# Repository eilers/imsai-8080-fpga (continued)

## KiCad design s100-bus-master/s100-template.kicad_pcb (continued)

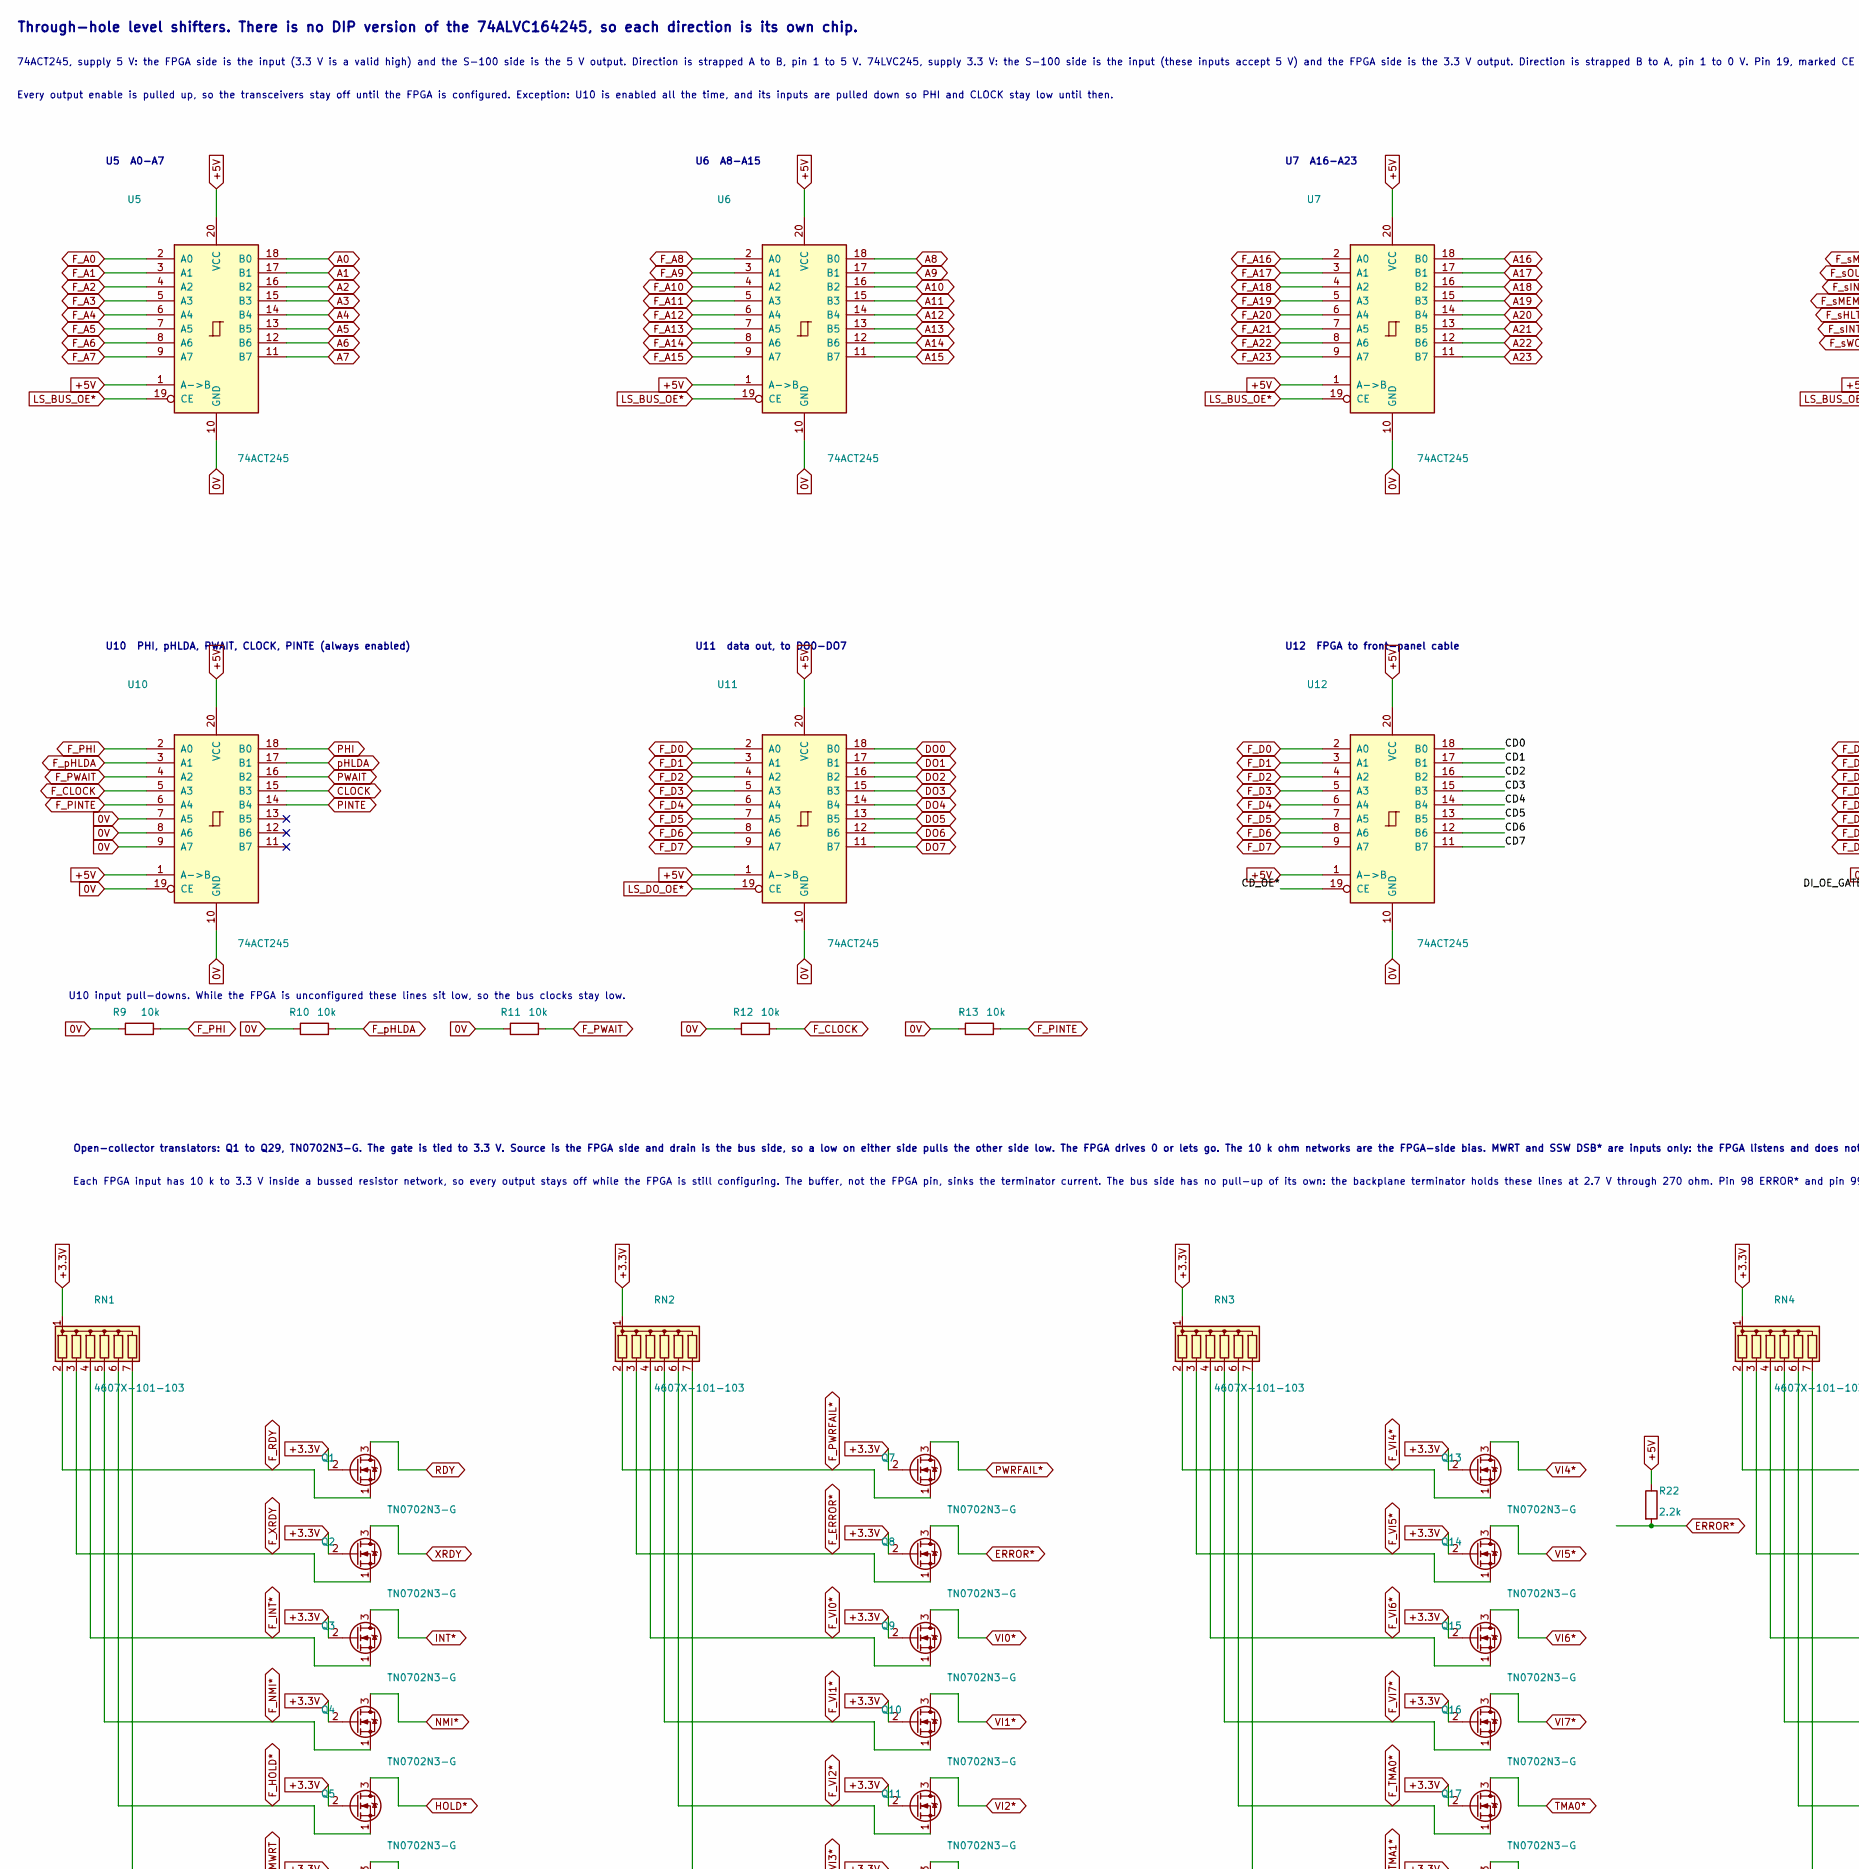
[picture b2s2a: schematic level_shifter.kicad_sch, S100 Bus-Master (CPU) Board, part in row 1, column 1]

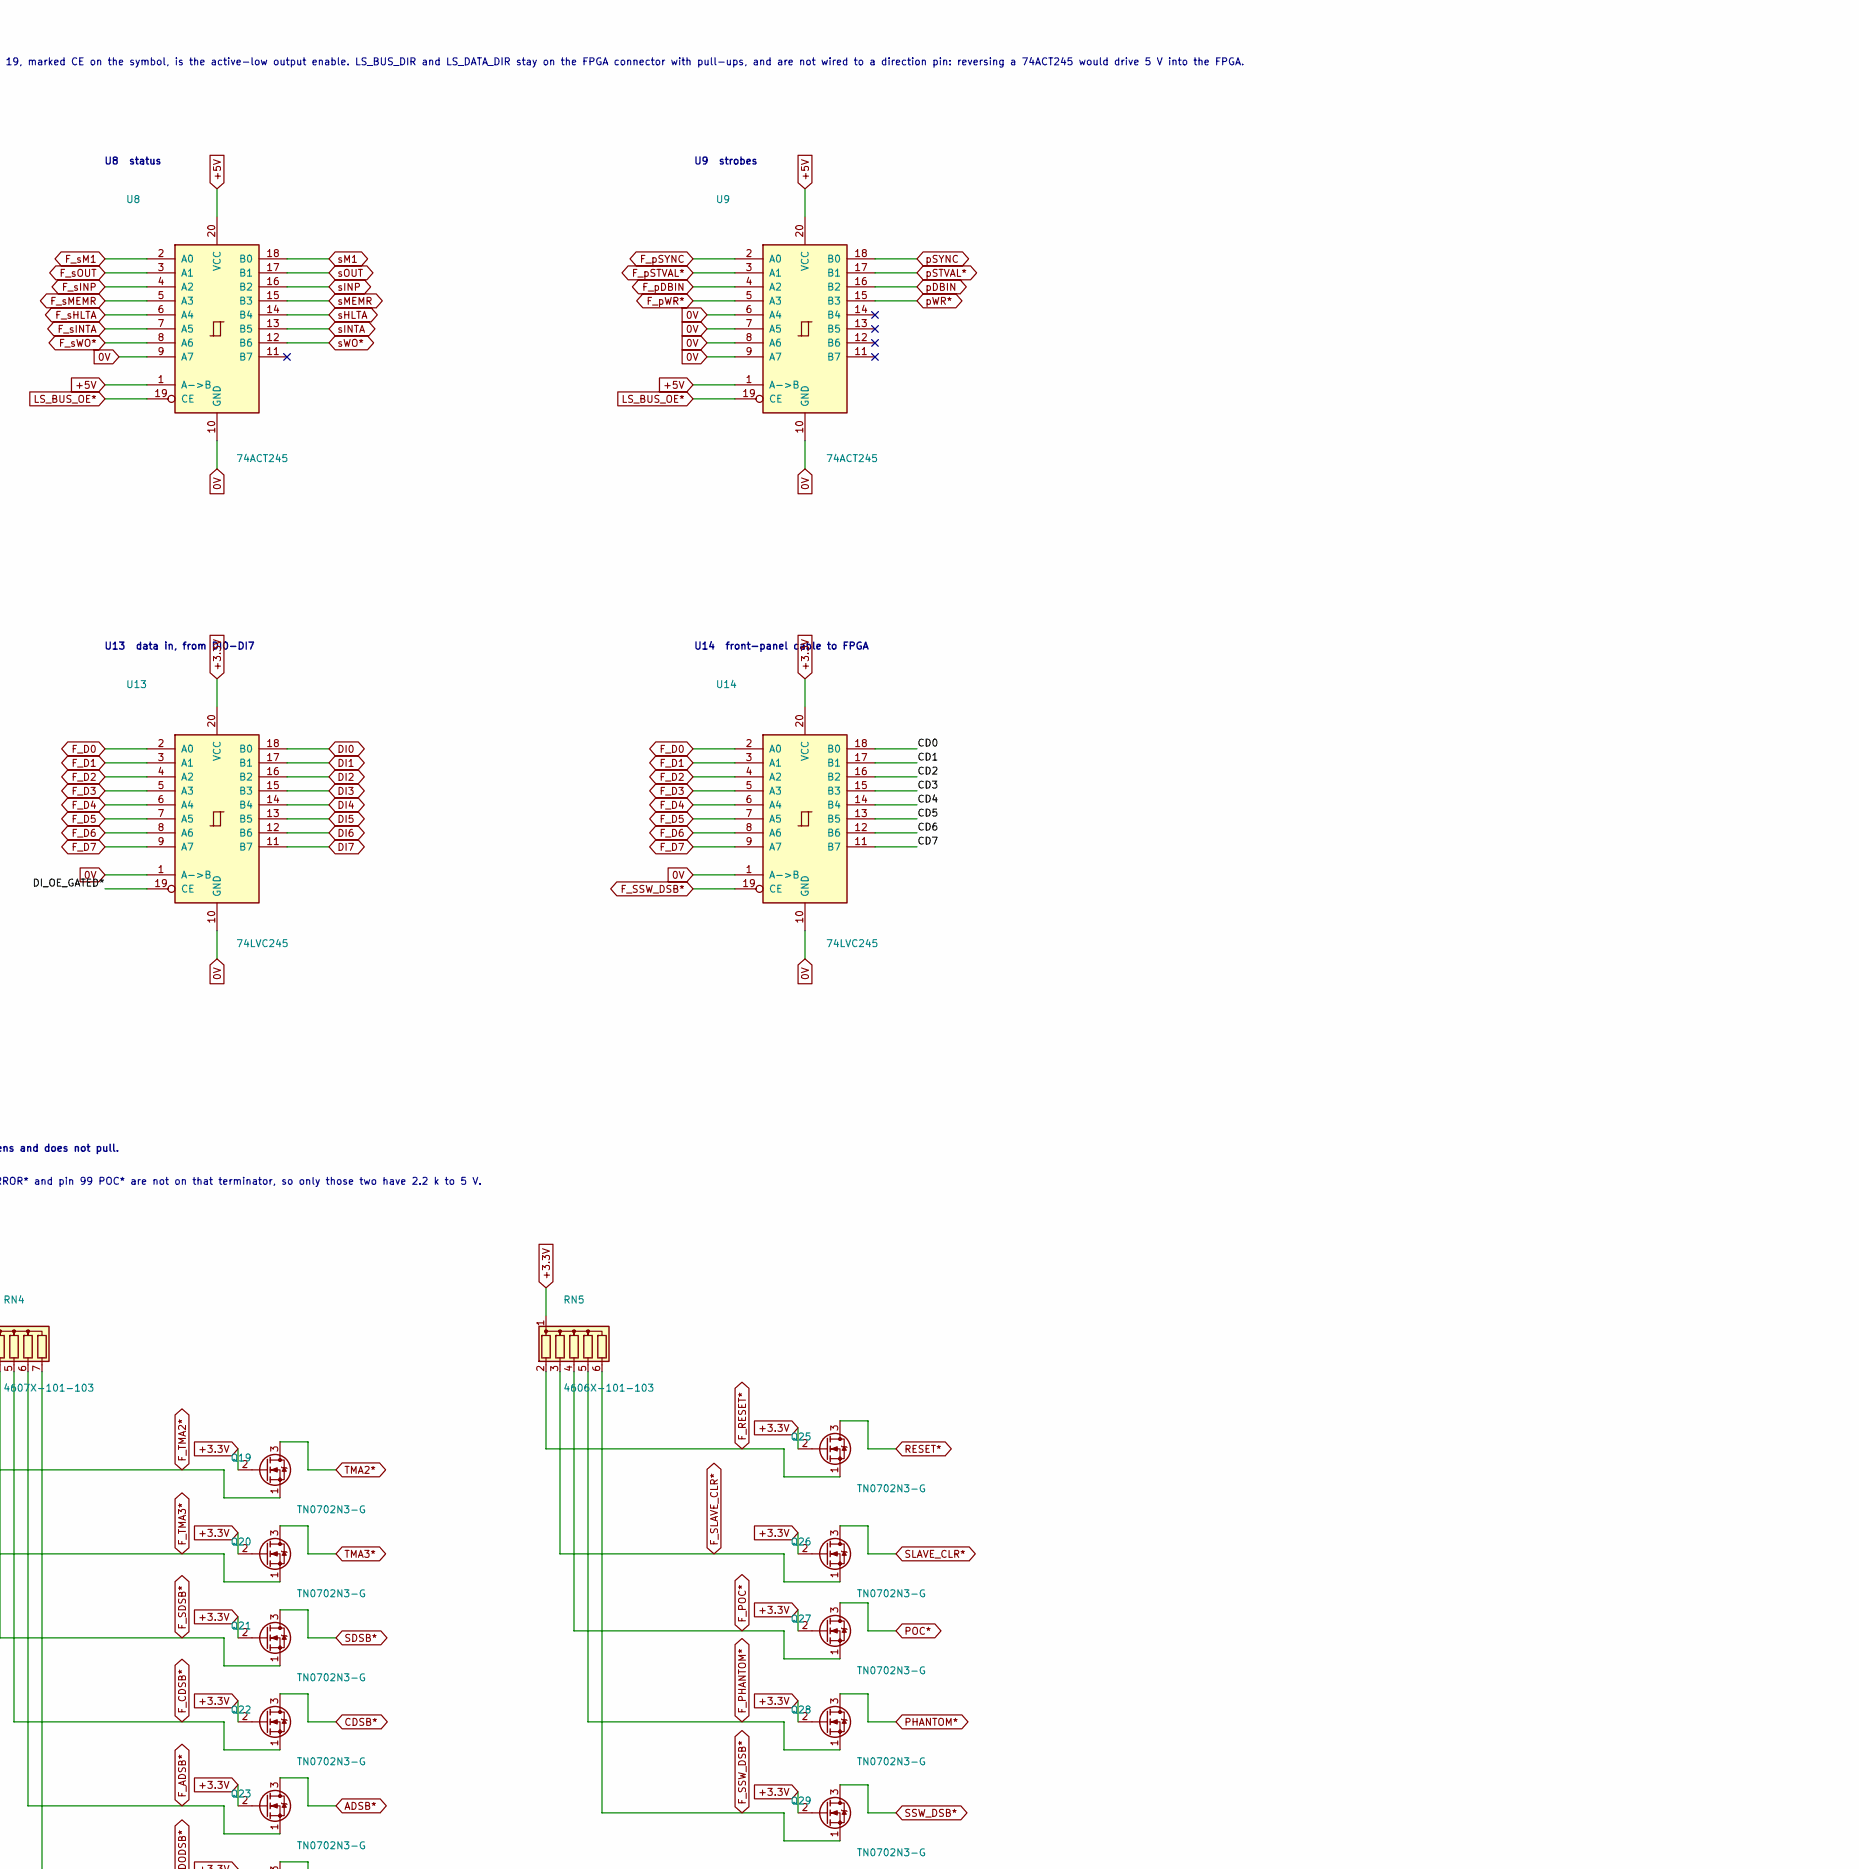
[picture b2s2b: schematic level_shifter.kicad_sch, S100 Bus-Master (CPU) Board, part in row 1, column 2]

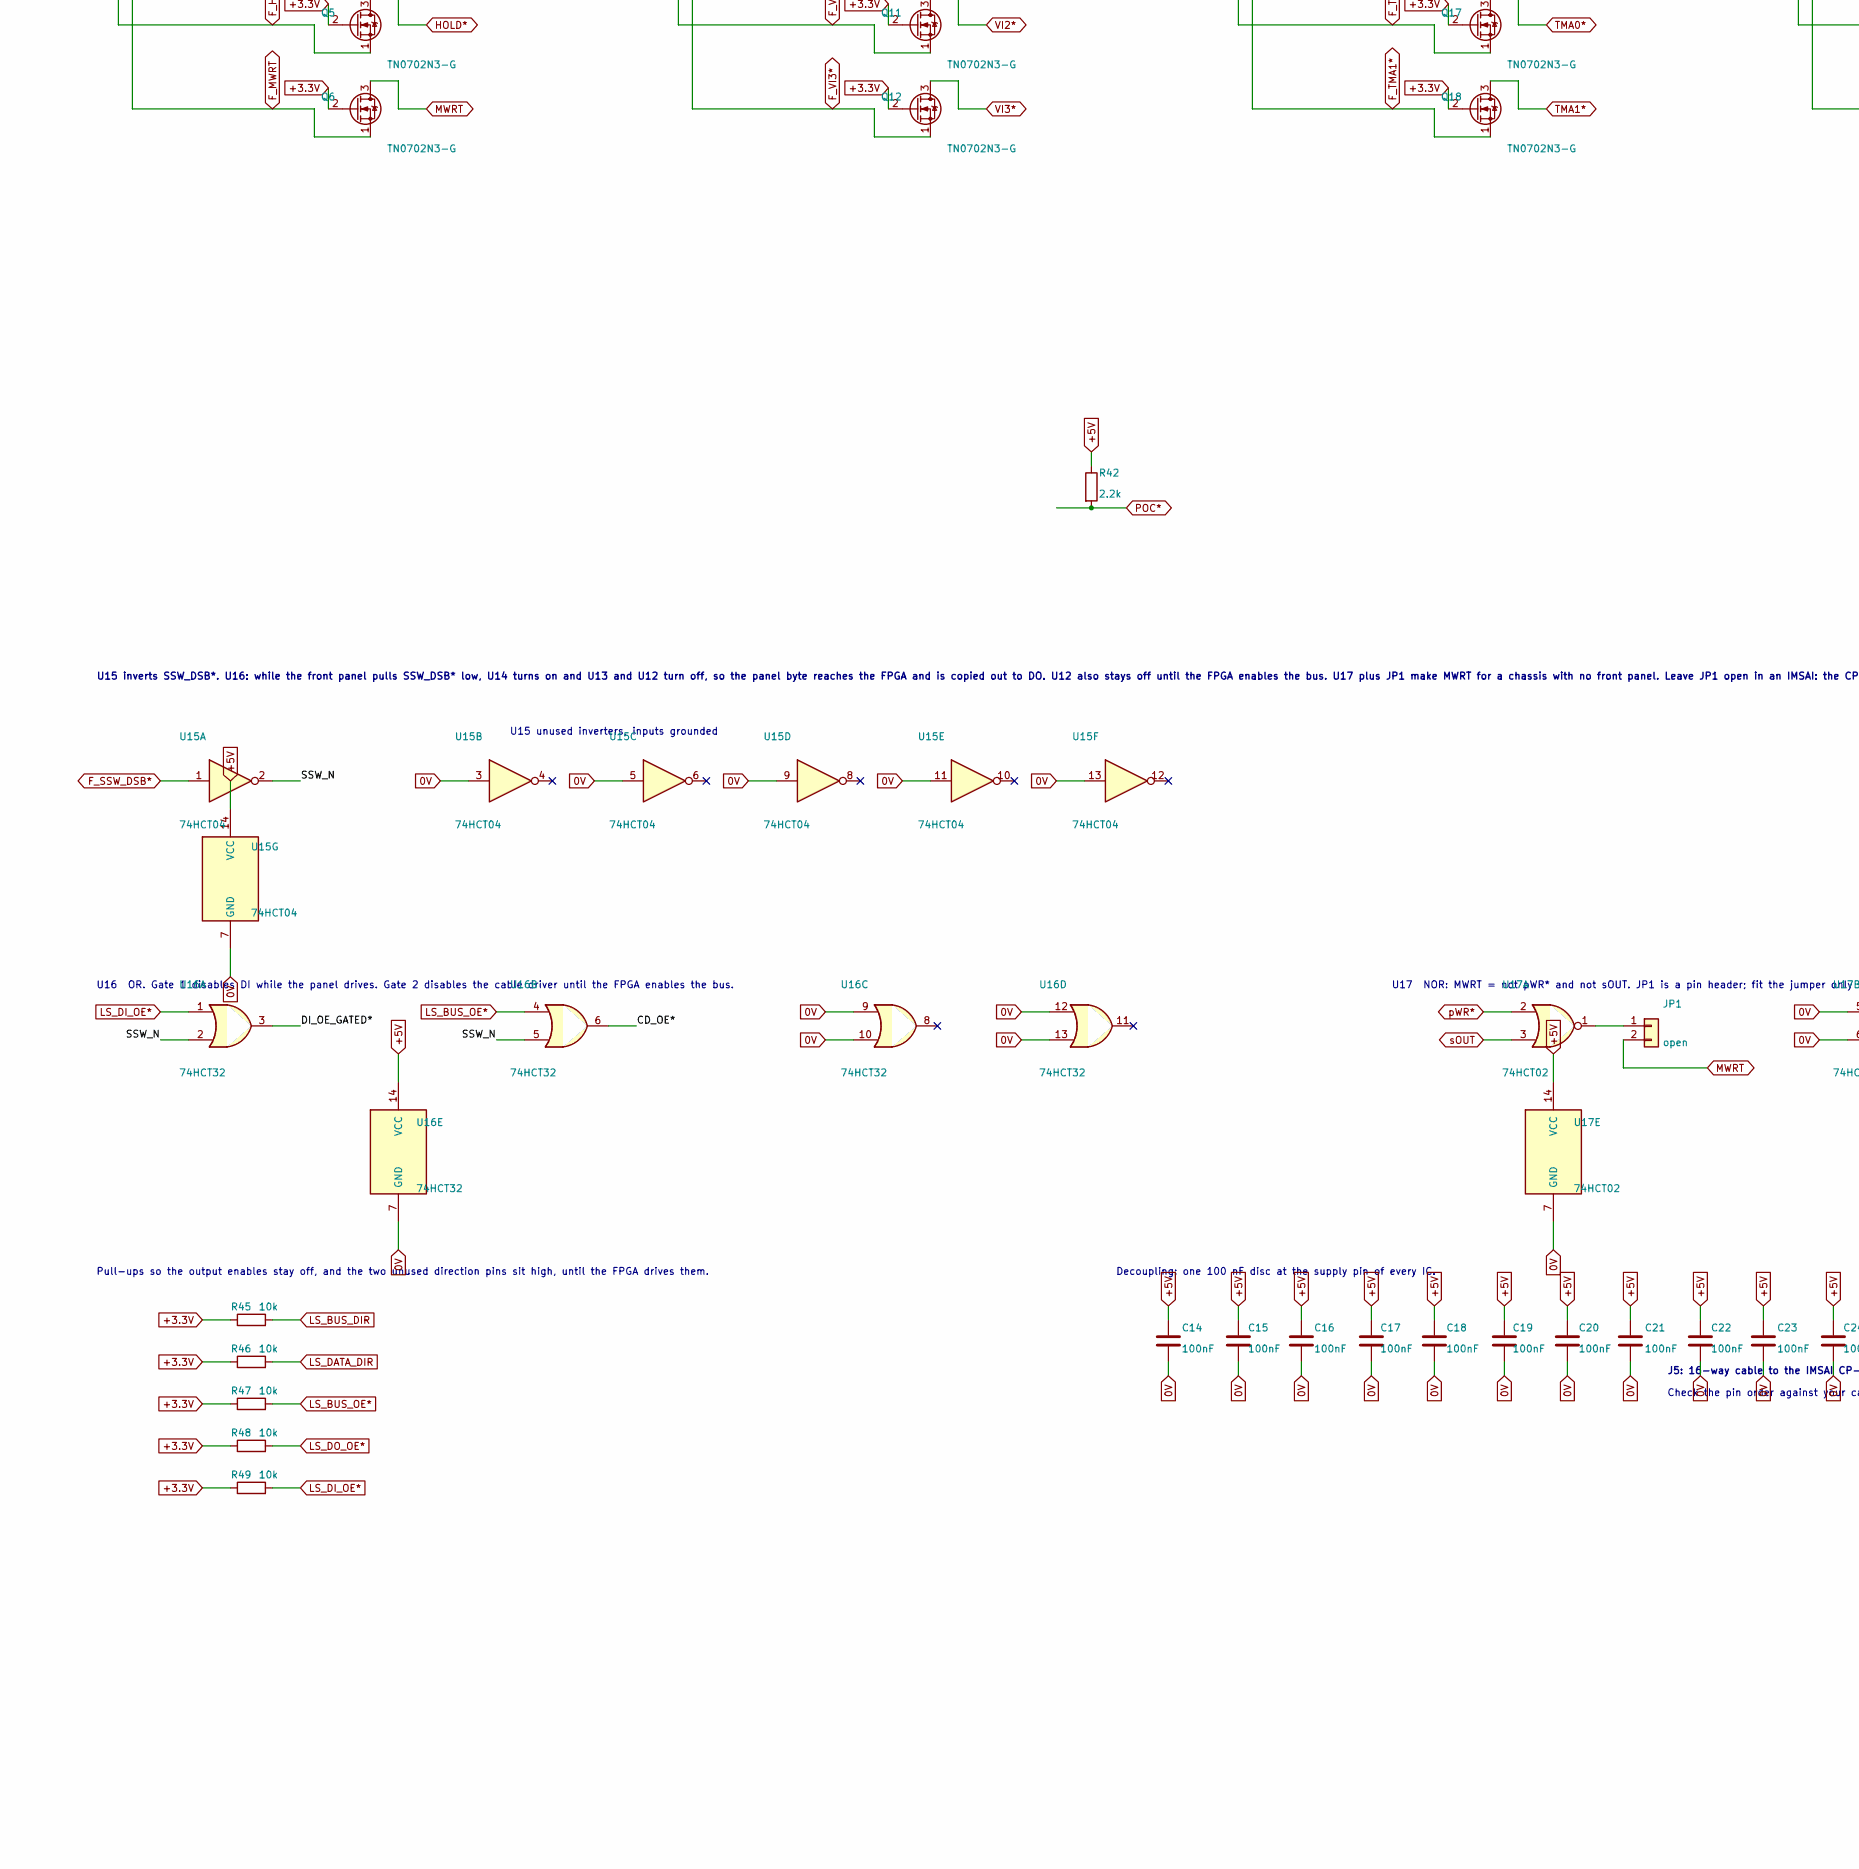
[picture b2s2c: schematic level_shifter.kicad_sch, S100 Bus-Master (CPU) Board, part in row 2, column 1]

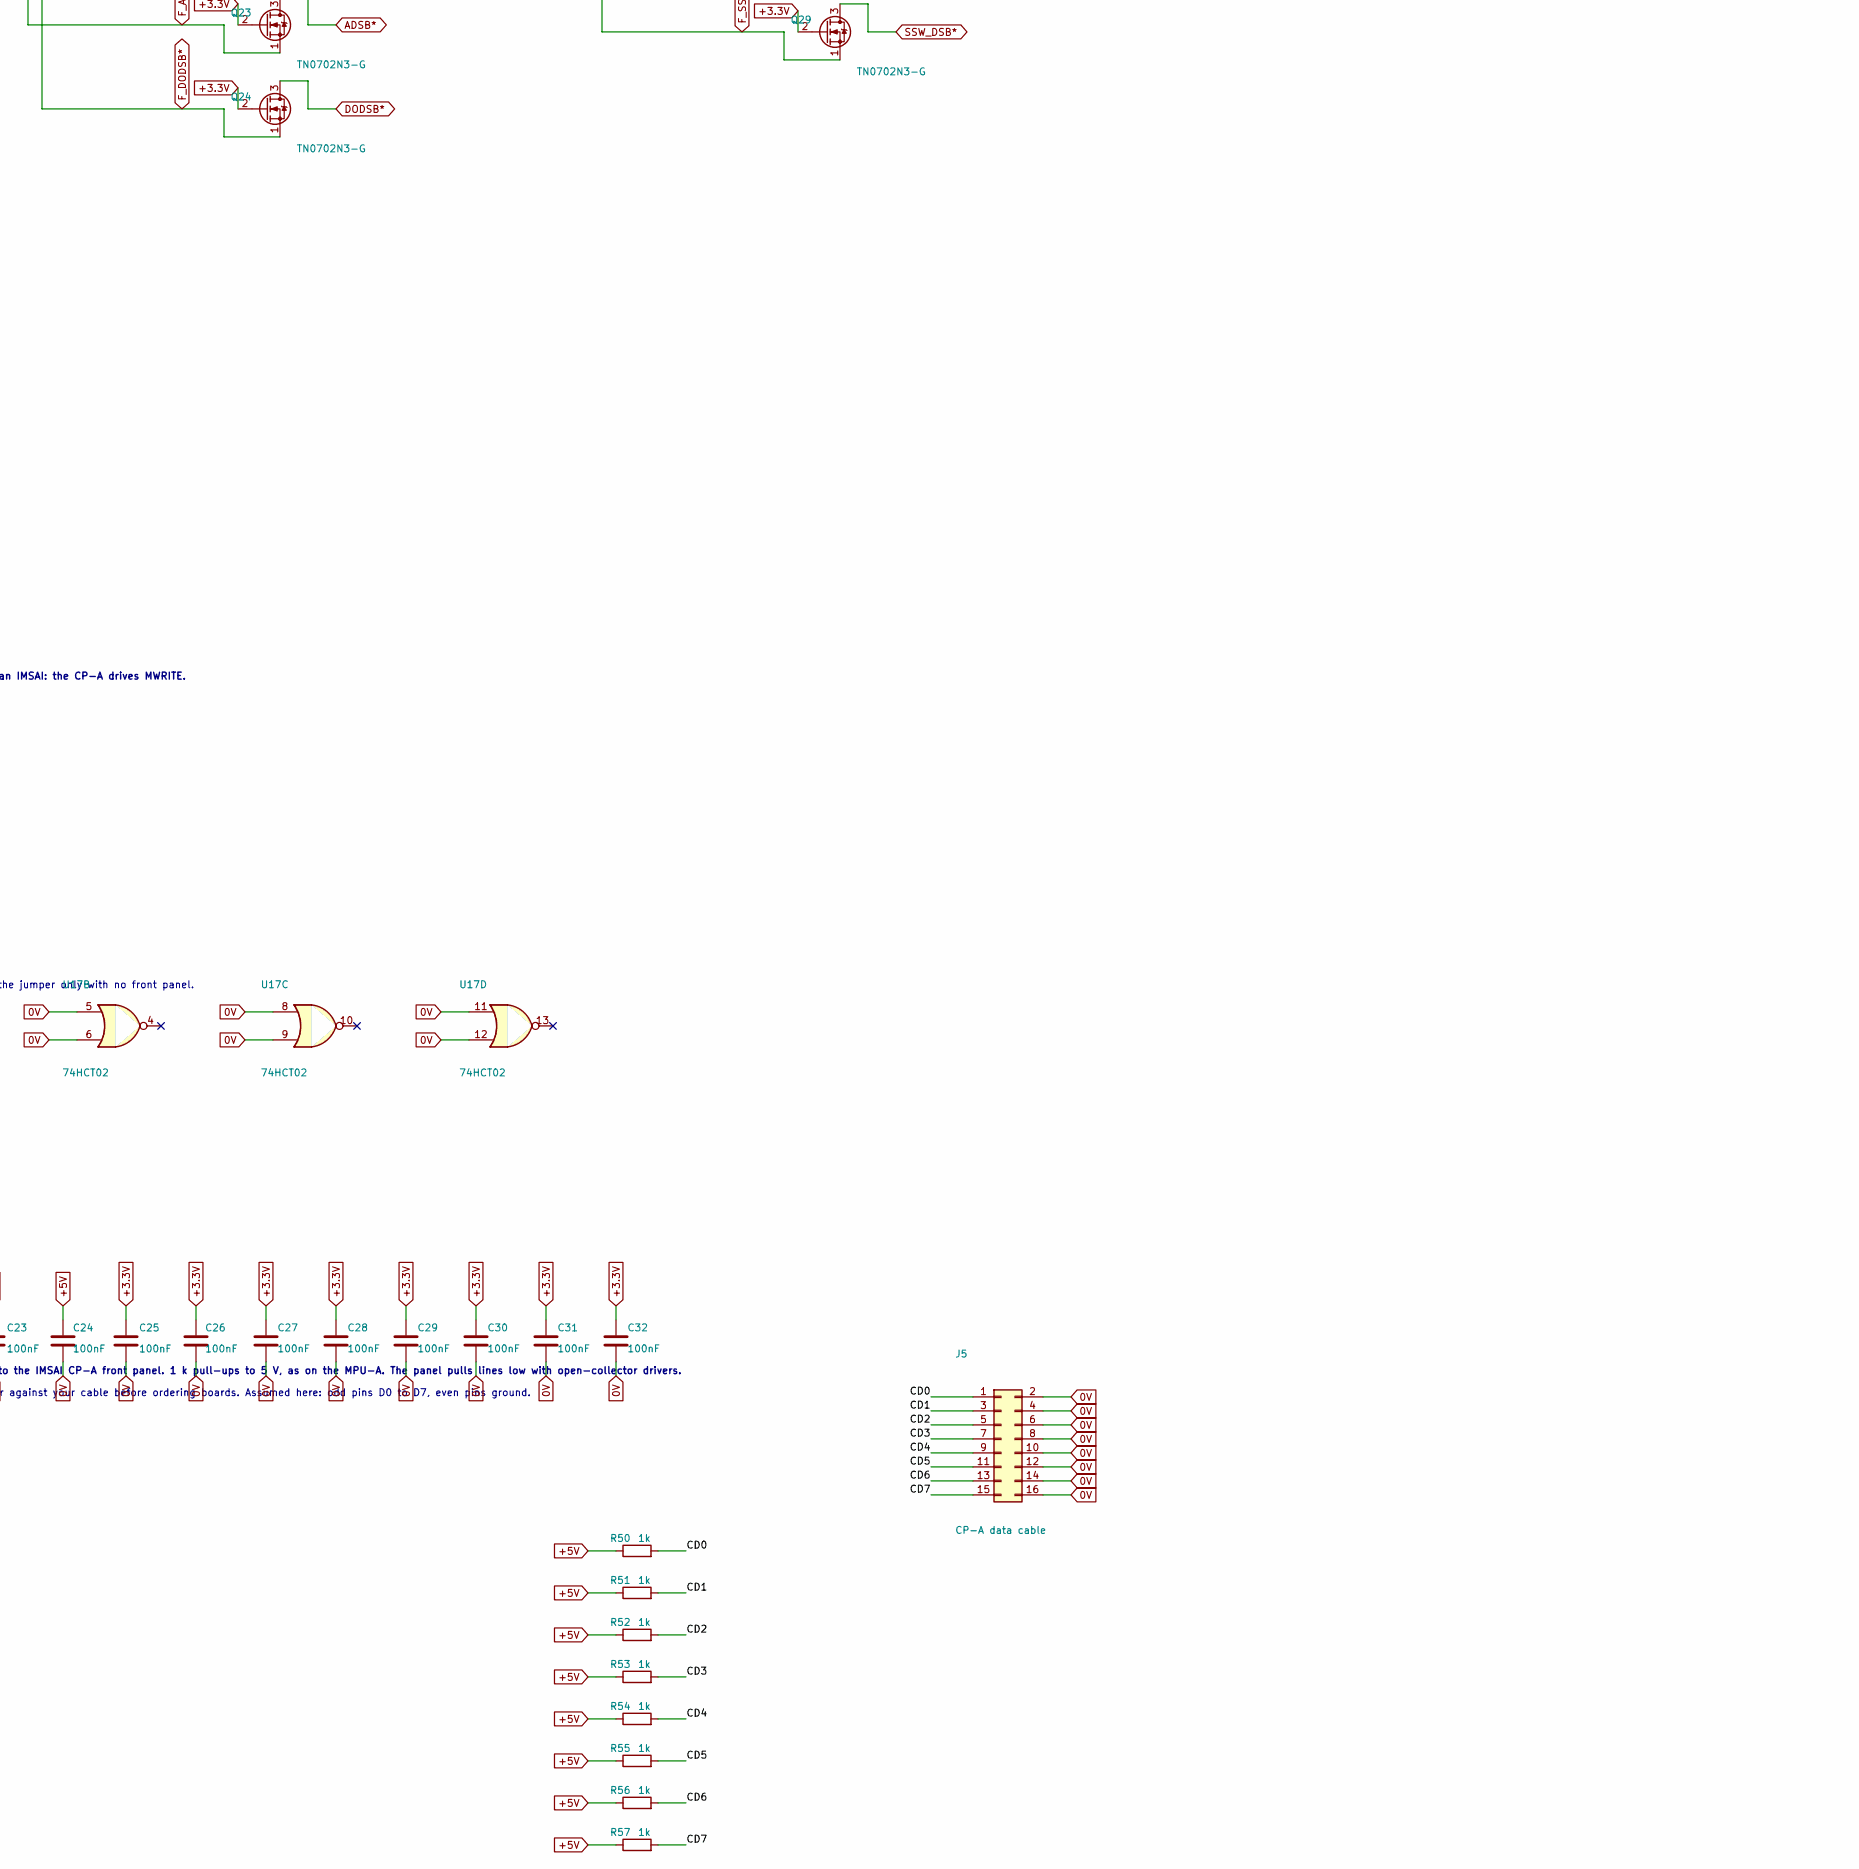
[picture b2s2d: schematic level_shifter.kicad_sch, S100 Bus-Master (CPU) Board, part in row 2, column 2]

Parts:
C14, C15, C16, C17, C18, C19, C20, C21, C22, C23, C24, C25, C26, C27, C28, C29, C30, C31, C32: 100nF; C_Disc_D5.0mm_W2.5mm_P5.00mm
J5: CP-A data cable; IDC-Header_2x08_P2.54mm_Vertical
JP1: open; PinHeader_1x02_P2.54mm_Vertical
Q1, Q2, Q3, Q4, Q5, Q6, Q7, Q8, Q9, Q10, Q11, Q12, Q13, Q14, Q15, Q16, Q17, Q18, Q19, Q20, Q21, Q22, Q23, Q24, Q25, Q26, Q27, Q28, Q29: TN0702N3-G; TO-92
R9, R10, R11, R12, R13, R45, R46, R47, R48, R49: 10k; R_Axial_DIN0207_L6.3mm_D2.5mm_P10.16mm_Horizontal
R22, R42: 2.2k; R_Axial_DIN0207_L6.3mm_D2.5mm_P10.16mm_Horizontal
R50, R51, R52, R53, R54, R55, R56, R57: 1k; R_Axial_DIN0207_L6.3mm_D2.5mm_P10.16mm_Horizontal
RN1, RN2, RN3, RN4: 4607X-101-103; R_Array_SIP7
RN5: 4606X-101-103; R_Array_SIP6
U5, U6, U7, U8, U9, U10, U11, U12: 74ACT245; DIP-20_W7.62mm
U13, U14: 74LVC245; DIP-20_W7.62mm
U15: 74HCT04; DIP-14_W7.62mm
U16: 74HCT32; DIP-14_W7.62mm
U17: 74HCT02; DIP-14_W7.62mm

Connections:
0V: C14.2, C15.2, C16.2, C17.2, C18.2, C19.2, C20.2, C21.2, C22.2, C23.2, C24.2, C25.2, C26.2, C27.2, C28.2, C29.2, C30.2, C31.2, C32.2, J5.2, J5.4, J5.6, J5.8, J5.10, J5.12, J5.14, J5.16, R9.1, R10.1, R11.1, R12.1, R13.1, U5.10 (GND), U6.10 (GND), U7.10 (GND), U8.9 (A7), U8.10 (GND), U9.6 (A4), U9.7 (A5), U9.8 (A6), U9.9 (A7), U9.10 (GND), U10.7 (A5), U10.8 (A6), U10.9 (A7), U10.10 (GND), U10.19 (CE), U11.10 (GND), U12.10 (GND), U13.1 (A->B), U13.10 (GND), U14.1 (A->B), U14.10 (GND), U15.3, U15.5, U15.7 (GND), U15.9, U15.11, U15.13, U16.7 (GND), U16.9, U16.10, U16.12, U16.13, U17.5, U17.6, U17.7 (GND), U17.8, U17.9, U17.11, U17.12; also elsewhere on the board
+3.3V: C25.1, C26.1, C27.1, C28.1, C29.1, C30.1, C31.1, C32.1, Q1.2 (G), Q2.2 (G), Q3.2 (G), Q4.2 (G), Q5.2 (G), Q6.2 (G), Q7.2 (G), Q8.2 (G), Q9.2 (G), Q10.2 (G), Q11.2 (G), Q12.2 (G), Q13.2 (G), Q14.2 (G), Q15.2 (G), Q16.2 (G), Q17.2 (G), Q18.2 (G), Q19.2 (G), Q20.2 (G), Q21.2 (G), Q22.2 (G), Q23.2 (G), Q24.2 (G), Q25.2 (G), Q26.2 (G), Q27.2 (G), Q28.2 (G), Q29.2 (G), R45.1, R46.1, R47.1, R48.1, R49.1, RN1.1 (common), RN2.1 (common), RN3.1 (common), RN4.1 (common), RN5.1 (common), U13.20 (VCC), U14.20 (VCC); also elsewhere on the board
+5V: C14.1, C15.1, C16.1, C17.1, C18.1, C19.1, C20.1, C21.1, C22.1, C23.1, C24.1, R22.1, R42.1, R50.1, R51.1, R52.1, R53.1, R54.1, R55.1, R56.1, R57.1, U5.1 (A->B), U5.20 (VCC), U6.1 (A->B), U6.20 (VCC), U7.1 (A->B), U7.20 (VCC), U8.1 (A->B), U8.20 (VCC), U9.1 (A->B), U9.20 (VCC), U10.1 (A->B), U10.20 (VCC), U11.1 (A->B), U11.20 (VCC), U12.1 (A->B), U12.20 (VCC), U15.14 (VCC), U16.14 (VCC), U17.14 (VCC); also elsewhere on the board
/Level Shifter/CD0: J5.1, R50.2, U12.18 (B0), U14.18 (B0)
/Level Shifter/CD1: J5.3, R51.2, U12.17 (B1), U14.17 (B1)
/Level Shifter/CD2: J5.5, R52.2, U12.16 (B2), U14.16 (B2)
/Level Shifter/CD3: J5.7, R53.2, U12.15 (B3), U14.15 (B3)
/Level Shifter/CD4: J5.9, R54.2, U12.14 (B4), U14.14 (B4)
/Level Shifter/CD5: J5.11, R55.2, U12.13 (B5), U14.13 (B5)
/Level Shifter/CD6: J5.13, R56.2, U12.12 (B6), U14.12 (B6)
/Level Shifter/CD7: J5.15, R57.2, U12.11 (B7), U14.11 (B7)
/Level Shifter/CD_OE*: U12.19 (CE), U16.6
/Level Shifter/DI_OE_GATED*: U13.19 (CE), U16.3
/Level Shifter/SSW_N: U15.2, U16.2, U16.5
A0: U5.18 (B0); also elsewhere on the board
A1: U5.17 (B1); also elsewhere on the board
A2: U5.16 (B2); also elsewhere on the board
A3: U5.15 (B3); also elsewhere on the board
A4: U5.14 (B4); also elsewhere on the board
A5: U5.13 (B5); also elsewhere on the board
A6: U5.12 (B6); also elsewhere on the board
A7: U5.11 (B7); also elsewhere on the board
A8: U6.18 (B0); also elsewhere on the board
A9: U6.17 (B1); also elsewhere on the board
A10: U6.16 (B2); also elsewhere on the board
A11: U6.15 (B3); also elsewhere on the board
A12: U6.14 (B4); also elsewhere on the board
A13: U6.13 (B5); also elsewhere on the board
A14: U6.12 (B6); also elsewhere on the board
A15: U6.11 (B7); also elsewhere on the board
A16: U7.18 (B0); also elsewhere on the board
A17: U7.17 (B1); also elsewhere on the board
A18: U7.16 (B2); also elsewhere on the board
A19: U7.15 (B3); also elsewhere on the board
A20: U7.14 (B4); also elsewhere on the board
A21: U7.13 (B5); also elsewhere on the board
A22: U7.12 (B6); also elsewhere on the board
A23: U7.11 (B7); also elsewhere on the board
ADSB*: Q23.3 (D); also elsewhere on the board
CDSB*: Q22.3 (D); also elsewhere on the board
CLOCK: U10.15 (B3); also elsewhere on the board
DI0: U13.18 (B0); also elsewhere on the board
DI1: U13.17 (B1); also elsewhere on the board
DI2: U13.16 (B2); also elsewhere on the board
DI3: U13.15 (B3); also elsewhere on the board
DI4: U13.14 (B4); also elsewhere on the board
DI5: U13.13 (B5); also elsewhere on the board
DI6: U13.12 (B6); also elsewhere on the board
DI7: U13.11 (B7); also elsewhere on the board
DO0: U11.18 (B0); also elsewhere on the board
DO1: U11.17 (B1); also elsewhere on the board
DO2: U11.16 (B2); also elsewhere on the board
DO3: U11.15 (B3); also elsewhere on the board
DO4: U11.14 (B4); also elsewhere on the board
DO5: U11.13 (B5); also elsewhere on the board
DO6: U11.12 (B6); also elsewhere on the board
DO7: U11.11 (B7); also elsewhere on the board
DODSB*: Q24.3 (D); also elsewhere on the board
ERROR*: Q8.3 (D), R22.2; also elsewhere on the board
F_A0: U5.2 (A0); also elsewhere on the board
F_A1: U5.3 (A1); also elsewhere on the board
F_A2: U5.4 (A2); also elsewhere on the board
F_A3: U5.5 (A3); also elsewhere on the board
F_A4: U5.6 (A4); also elsewhere on the board
F_A5: U5.7 (A5); also elsewhere on the board
F_A6: U5.8 (A6); also elsewhere on the board
F_A7: U5.9 (A7); also elsewhere on the board
F_A8: U6.2 (A0); also elsewhere on the board
F_A9: U6.3 (A1); also elsewhere on the board
F_A10: U6.4 (A2); also elsewhere on the board
F_A11: U6.5 (A3); also elsewhere on the board
F_A12: U6.6 (A4); also elsewhere on the board
F_A13: U6.7 (A5); also elsewhere on the board
F_A14: U6.8 (A6); also elsewhere on the board
F_A15: U6.9 (A7); also elsewhere on the board
F_A16: U7.2 (A0); also elsewhere on the board
F_A17: U7.3 (A1); also elsewhere on the board
F_A18: U7.4 (A2); also elsewhere on the board
F_A19: U7.5 (A3); also elsewhere on the board
F_A20: U7.6 (A4); also elsewhere on the board
F_A21: U7.7 (A5); also elsewhere on the board
F_A22: U7.8 (A6); also elsewhere on the board
F_A23: U7.9 (A7); also elsewhere on the board
F_ADSB*: Q23.1 (S), RN4.6 (R5); also elsewhere on the board
F_CDSB*: Q22.1 (S), RN4.5 (R4); also elsewhere on the board
F_CLOCK: R12.2, U10.5 (A3); also elsewhere on the board
F_D0: U11.2 (A0), U12.2 (A0), U13.2 (A0), U14.2 (A0); also elsewhere on the board
F_D1: U11.3 (A1), U12.3 (A1), U13.3 (A1), U14.3 (A1); also elsewhere on the board
F_D2: U11.4 (A2), U12.4 (A2), U13.4 (A2), U14.4 (A2); also elsewhere on the board
F_D3: U11.5 (A3), U12.5 (A3), U13.5 (A3), U14.5 (A3); also elsewhere on the board
F_D4: U11.6 (A4), U12.6 (A4), U13.6 (A4), U14.6 (A4); also elsewhere on the board
F_D5: U11.7 (A5), U12.7 (A5), U13.7 (A5), U14.7 (A5); also elsewhere on the board
F_D6: U11.8 (A6), U12.8 (A6), U13.8 (A6), U14.8 (A6); also elsewhere on the board
F_D7: U11.9 (A7), U12.9 (A7), U13.9 (A7), U14.9 (A7); also elsewhere on the board
F_DODSB*: Q24.1 (S), RN4.7 (R6); also elsewhere on the board
F_ERROR*: Q8.1 (S), RN2.3 (R2); also elsewhere on the board
F_HOLD*: Q5.1 (S), RN1.6 (R5); also elsewhere on the board
F_INT*: Q3.1 (S), RN1.4 (R3); also elsewhere on the board
F_MWRT: Q6.1 (S), RN1.7 (R6); also elsewhere on the board
F_NMI*: Q4.1 (S), RN1.5 (R4); also elsewhere on the board
F_PHANTOM*: Q28.1 (S), RN5.5 (R4); also elsewhere on the board
F_PHI: R9.2, U10.2 (A0); also elsewhere on the board
F_PINTE: R13.2, U10.6 (A4); also elsewhere on the board
F_POC*: Q27.1 (S), RN5.4 (R3); also elsewhere on the board
F_PWAIT: R11.2, U10.4 (A2); also elsewhere on the board
F_PWRFAIL*: Q7.1 (S), RN2.2 (R1); also elsewhere on the board
F_RDY: Q1.1 (S), RN1.2 (R1); also elsewhere on the board
F_RESET*: Q25.1 (S), RN5.2 (R1); also elsewhere on the board
F_SDSB*: Q21.1 (S), RN4.4 (R3); also elsewhere on the board
F_SLAVE_CLR*: Q26.1 (S), RN5.3 (R2); also elsewhere on the board
F_SSW_DSB*: Q29.1 (S), RN5.6 (R5), U14.19 (CE), U15.1; also elsewhere on the board
F_TMA0*: Q17.1 (S), RN3.6 (R5); also elsewhere on the board
F_TMA1*: Q18.1 (S), RN3.7 (R6); also elsewhere on the board
F_TMA2*: Q19.1 (S), RN4.2 (R1); also elsewhere on the board
F_TMA3*: Q20.1 (S), RN4.3 (R2); also elsewhere on the board
F_VI0*: Q9.1 (S), RN2.4 (R3); also elsewhere on the board
F_VI1*: Q10.1 (S), RN2.5 (R4); also elsewhere on the board
F_VI2*: Q11.1 (S), RN2.6 (R5); also elsewhere on the board
F_VI3*: Q12.1 (S), RN2.7 (R6); also elsewhere on the board
F_VI4*: Q13.1 (S), RN3.2 (R1); also elsewhere on the board
F_VI5*: Q14.1 (S), RN3.3 (R2); also elsewhere on the board
F_VI6*: Q15.1 (S), RN3.4 (R3); also elsewhere on the board
F_VI7*: Q16.1 (S), RN3.5 (R4); also elsewhere on the board
F_XRDY: Q2.1 (S), RN1.3 (R2); also elsewhere on the board
F_pDBIN: U9.4 (A2); also elsewhere on the board
F_pHLDA: R10.2, U10.3 (A1); also elsewhere on the board
F_pSTVAL*: U9.3 (A1); also elsewhere on the board
F_pSYNC: U9.2 (A0); also elsewhere on the board
F_pWR*: U9.5 (A3); also elsewhere on the board
F_sHLTA: U8.6 (A4); also elsewhere on the board
F_sINP: U8.4 (A2); also elsewhere on the board
F_sINTA: U8.7 (A5); also elsewhere on the board
F_sM1: U8.2 (A0); also elsewhere on the board
F_sMEMR: U8.5 (A3); also elsewhere on the board
F_sOUT: U8.3 (A1); also elsewhere on the board
F_sWO*: U8.8 (A6); also elsewhere on the board
HOLD*: Q5.3 (D); also elsewhere on the board
INT*: Q3.3 (D); also elsewhere on the board
LS_BUS_DIR: R45.2; also elsewhere on the board
LS_BUS_OE*: R47.2, U5.19 (CE), U6.19 (CE), U7.19 (CE), U8.19 (CE), U9.19 (CE), U16.4; also elsewhere on the board
LS_DATA_DIR: R46.2; also elsewhere on the board
LS_DI_OE*: R49.2, U16.1; also elsewhere on the board
LS_DO_OE*: R48.2, U11.19 (CE); also elsewhere on the board
MWRT: JP1.2, Q6.3 (D); also elsewhere on the board
NMI*: Q4.3 (D); also elsewhere on the board
unnamed: JP1.1, U17.1
PHANTOM*: Q28.3 (D); also elsewhere on the board
PHI: U10.18 (B0); also elsewhere on the board
PINTE: U10.14 (B4); also elsewhere on the board
POC*: Q27.3 (D), R42.2; also elsewhere on the board
PWAIT: U10.16 (B2); also elsewhere on the board
PWRFAIL*: Q7.3 (D); also elsewhere on the board
RDY: Q1.3 (D); also elsewhere on the board
RESET*: Q25.3 (D); also elsewhere on the board
SDSB*: Q21.3 (D); also elsewhere on the board
SLAVE_CLR*: Q26.3 (D); also elsewhere on the board
SSW_DSB*: Q29.3 (D); also elsewhere on the board
TMA0*: Q17.3 (D); also elsewhere on the board
TMA1*: Q18.3 (D); also elsewhere on the board
TMA2*: Q19.3 (D); also elsewhere on the board
TMA3*: Q20.3 (D); also elsewhere on the board
VI0*: Q9.3 (D); also elsewhere on the board
VI1*: Q10.3 (D); also elsewhere on the board
VI2*: Q11.3 (D); also elsewhere on the board
VI3*: Q12.3 (D); also elsewhere on the board
VI4*: Q13.3 (D); also elsewhere on the board
VI5*: Q14.3 (D); also elsewhere on the board
VI6*: Q15.3 (D); also elsewhere on the board
VI7*: Q16.3 (D); also elsewhere on the board
XRDY: Q2.3 (D); also elsewhere on the board
pDBIN: U9.16 (B2); also elsewhere on the board
pHLDA: U10.17 (B1); also elsewhere on the board
pSTVAL*: U9.17 (B1); also elsewhere on the board
pSYNC: U9.18 (B0); also elsewhere on the board
pWR*: U9.15 (B3), U17.2; also elsewhere on the board
sHLTA: U8.14 (B4); also elsewhere on the board
sINP: U8.16 (B2); also elsewhere on the board
sINTA: U8.13 (B5); also elsewhere on the board
sM1: U8.18 (B0); also elsewhere on the board
sMEMR: U8.15 (B3); also elsewhere on the board
sOUT: U8.17 (B1), U17.3; also elsewhere on the board
sWO*: U8.12 (B6); also elsewhere on the board

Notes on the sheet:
Through-hole level shifters. There is no DIP version of the 74ALVC164245, so each direction is its own chip.
U17 NOR: MWRT = not pWR* and not sOUT. JP1 is a pin header; fit the jumper only with no front panel.
U15 unused inverters, inputs grounded
74ACT245, supply 5 V: the FPGA side is the input (3.3 V is a valid high) and the S-100 side is the 5 V output. Direction is strapped A to B, pin 1 to 5 V. 74LVC245, supply 3.3 V: the S-100 side is the input (these inputs accept 5 V) and the FPGA side is the 3.3 V output. Direction is strapped B to 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
U9 strobes
U7 A16-A23
Each FPGA input has 10 k to 3.3 V inside a bussed resistor network, so every output stays off while the FPGA is still configuring. The buffer, not the FPGA pin, sinks the terminator current. The bus side has no pull-up of its own: the backplane terminator holds these lines at 2.7 V through 270 ohm.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
J5: 16-way cable to the IMSAI CP-A front panel. 1 k pull-ups to 5 V, as on the MPU-A. The panel pulls lines low with open-collector drivers.
U10 PHI, pHLDA, PWAIT, CLOCK, PINTE (always enabled)
U13 data in, from DI0-DI7
U15 inverts SSW_DSB*. U16: while the front panel pulls SSW_DSB* low, U14 turns on and U13 and U12 turn off, so the panel byte reaches the FPGA and is copied out to DO. U12 also stays off until the FPGA enables the bus. U17 plus JP1 make MWRT for a chassis with no front panel. Leave JP1 open in an I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
U10 input pull-downs. While the FPGA is unconfigured these lines sit low, so the bus clocks stay low.
Decoupling: one 100 nF disc at the supply pin of every IC.
U5 A0-A7
U8 status
U12 FPGA to front-panel cable
Check the pin order against your cable before ordering boards. Assumed here: odd pins D0 to D7, even pins ground.
U14 front-panel cable to FPGA
Every output enable is pulled up, so the transceivers stay off until the FPGA is configured. Exception: U10 is enabled all the time, and its inputs are pulled down so PHI and CLOCK stay low until then.
U16 OR. Gate 1 disables DI while the panel drives. Gate 2 disables the cable driver until the FPGA enables the bus.
Pull-ups so the output enables stay off, and the two unused direction pins sit high, until the FPGA drives them.
U6 A8-A15
U11 data out, to DO0-DO7
Open-collector translators: Q1 to Q29, TN0702N3-G. The gate is tied to 3.3 V. Source is the FPGA side and drain is the bus side, so a low on either side pulls the other side low. The FPGA drives 0 or lets go. The 10 k ohm networks are the FPGA-side bias. MWRT and SSW DSB* are inputs only: the FPGA 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
